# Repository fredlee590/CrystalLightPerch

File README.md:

# CrystalLightPerch
Fancy nightlight that responds to light and external sensor (TBD)

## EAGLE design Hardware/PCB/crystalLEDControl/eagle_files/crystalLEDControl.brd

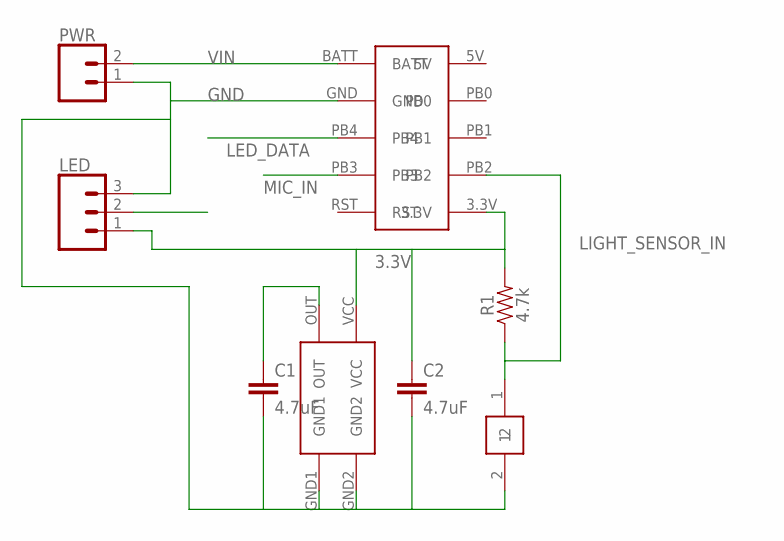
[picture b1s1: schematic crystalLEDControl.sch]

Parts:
A1: SPW2430
C1, C2: 4.7uF; 0603
LED: CONN_03; 1X03
MCU1: ARDUINO_TRINKET
PC1: PDV-P8101; PHOTOCELL_CERAMIC
PWR: CONN_02; 1X02
R1: 4.7k; 0603

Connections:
3.3V: A1.VCC, C2.1, LED.1, MCU1.3.3V, R1.2
GND: A1.GND1, A1.GND2, C1.2, C2.2, LED.3, MCU1.GND, PC1.2, PWR.1
LED_DATA: LED.2, MCU1.PB4
LIGHT_SENSOR_IN: MCU1.PB2, PC1.1, R1.1
MIC_IN: A1.OUT, C1.1, MCU1.PB3
VIN: MCU1.BATT, PWR.2

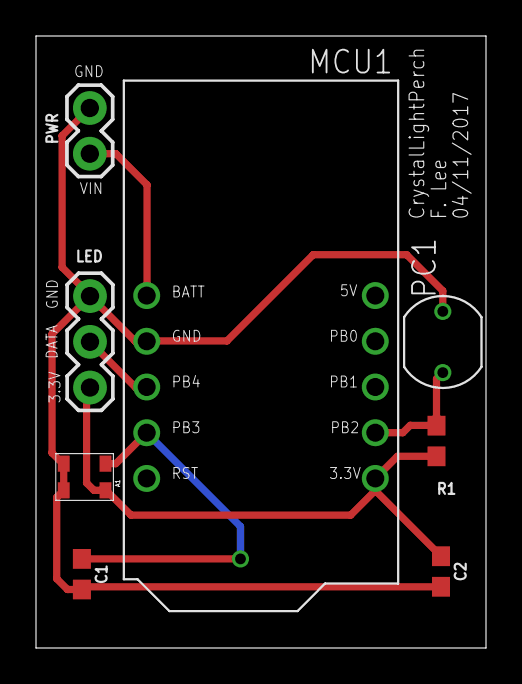
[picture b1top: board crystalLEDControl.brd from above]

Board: 2 copper layers, 25.0 x 34.0 mm, 8 parts (0 on the bottom side), 6 nets.

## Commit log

2017-03-09 Initial check in of state of the project. 3D model for perch, Planning docs for PCB, and Arduino sketch
2017-03-22 Initial check in of crystalLEDControl schematic and board. A good sprint done before routing.
2017-03-22 Routing complete. Pin labels as well.
2017-03-22 Add project description.
2017-03-23 Make version text smaller.
2017-04-12 Narrow board to fit better in 3D printed part.
2017-04-14 Add timeout of 10 minutes and set up some use of microphone analog input.
2017-05-23 Add MIMS microphone and support directly to board.
2017-06-14 Add software control for crystal light perch. Enabled ambient light detection.

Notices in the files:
parts and their libraries:
SparkFun-Connectors: Licensing: Creative Commons ShareAlike 4.0 International - https://creativecommons.org/licenses/by-sa/4.0
